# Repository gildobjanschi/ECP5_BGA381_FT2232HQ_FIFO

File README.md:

# ECP5/FT2232HQ Software & Hardware
This project implements a High Speed USB device using a FT2232HQ operating in synchronous FIFO mode coupled with a Lattice Semiconductor ECP5 FPGA. 

## Software
Read all the details of the bring-up steps and test code in the [Wiki](https://github.com/gildobjanschi/ECP5_BGA381_FT2232HQ_FIFO/wiki).

The diagram below will help you understand the software architecture and navigate the Verilog and C source code a bit easier.

## Hardware
The board is fully functional. An [extension board](https://github.com/gildobjanschi/ECP5_BGA381_FT2232HQ_FIFO_EXT) was developed to help validate the design.

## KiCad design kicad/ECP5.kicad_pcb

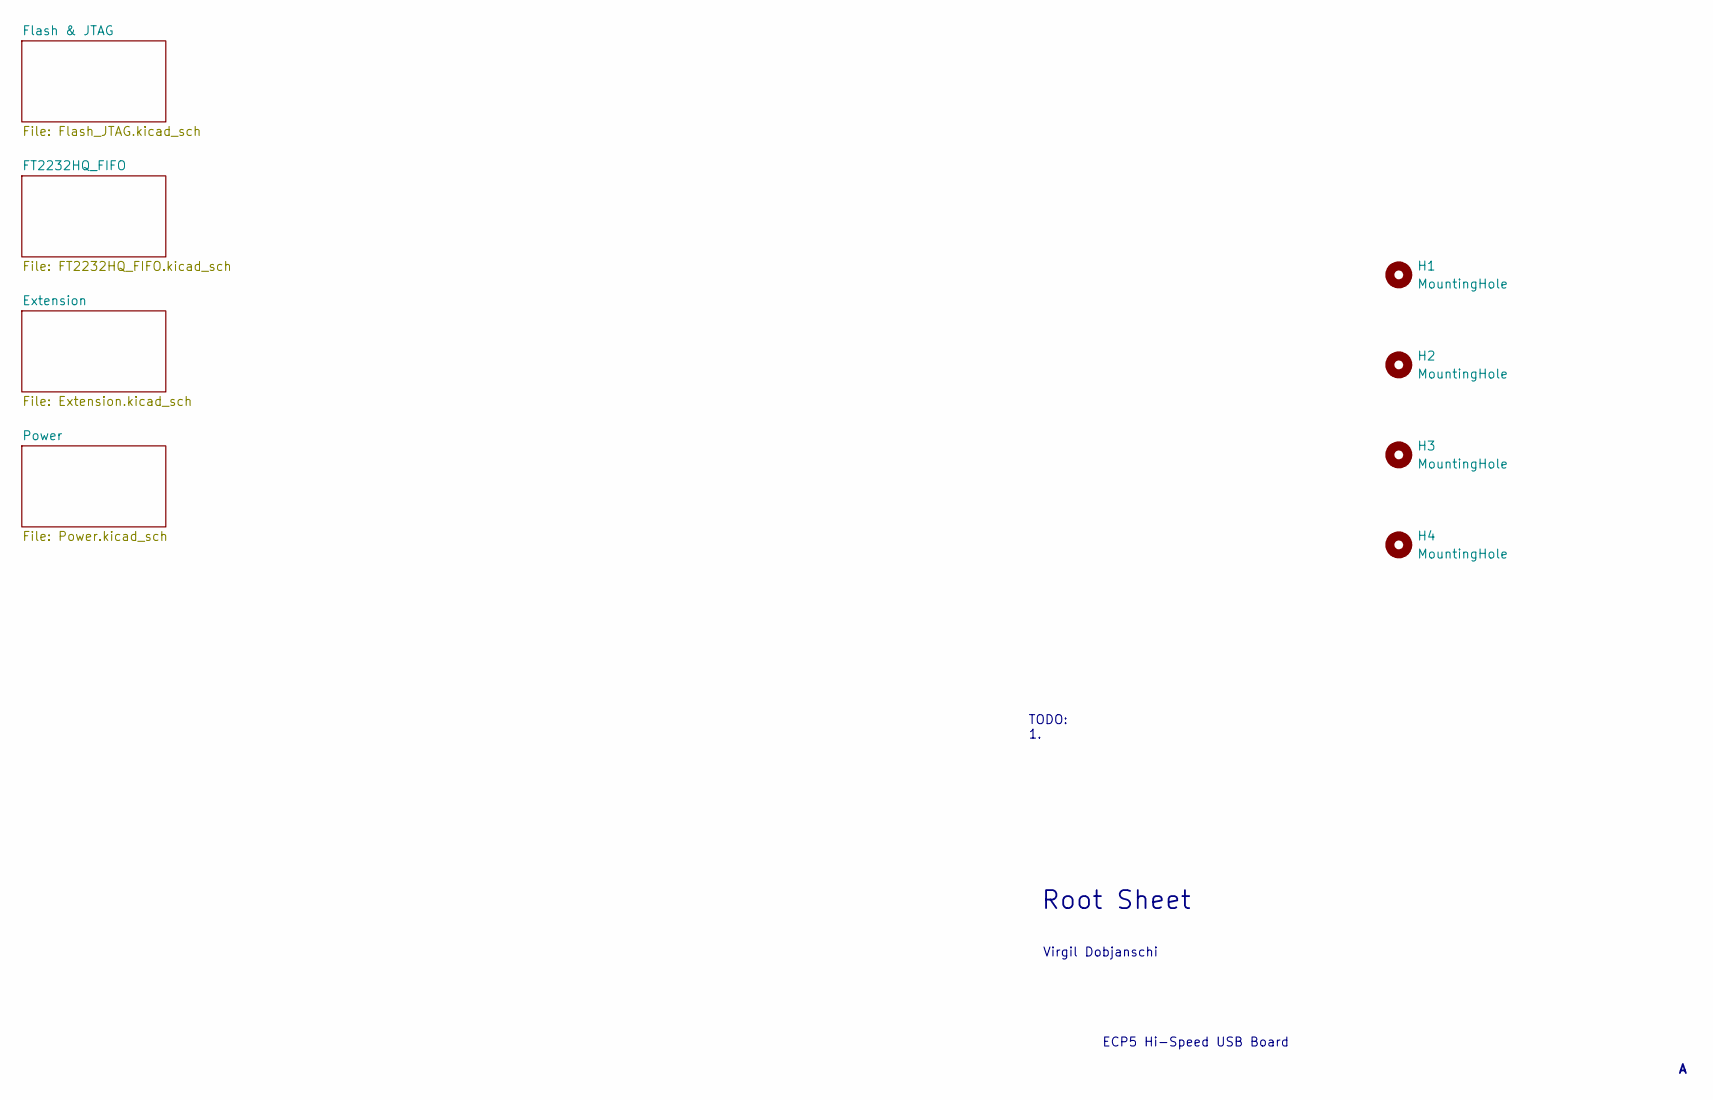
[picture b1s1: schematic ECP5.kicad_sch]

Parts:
H1, H2, H3, H4: MountingHole; MountingHole_3.2mm_M3

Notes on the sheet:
ECP5 Hi-Speed USB Board
Root Sheet
Virgil Dobjanschi
TODO: 1.

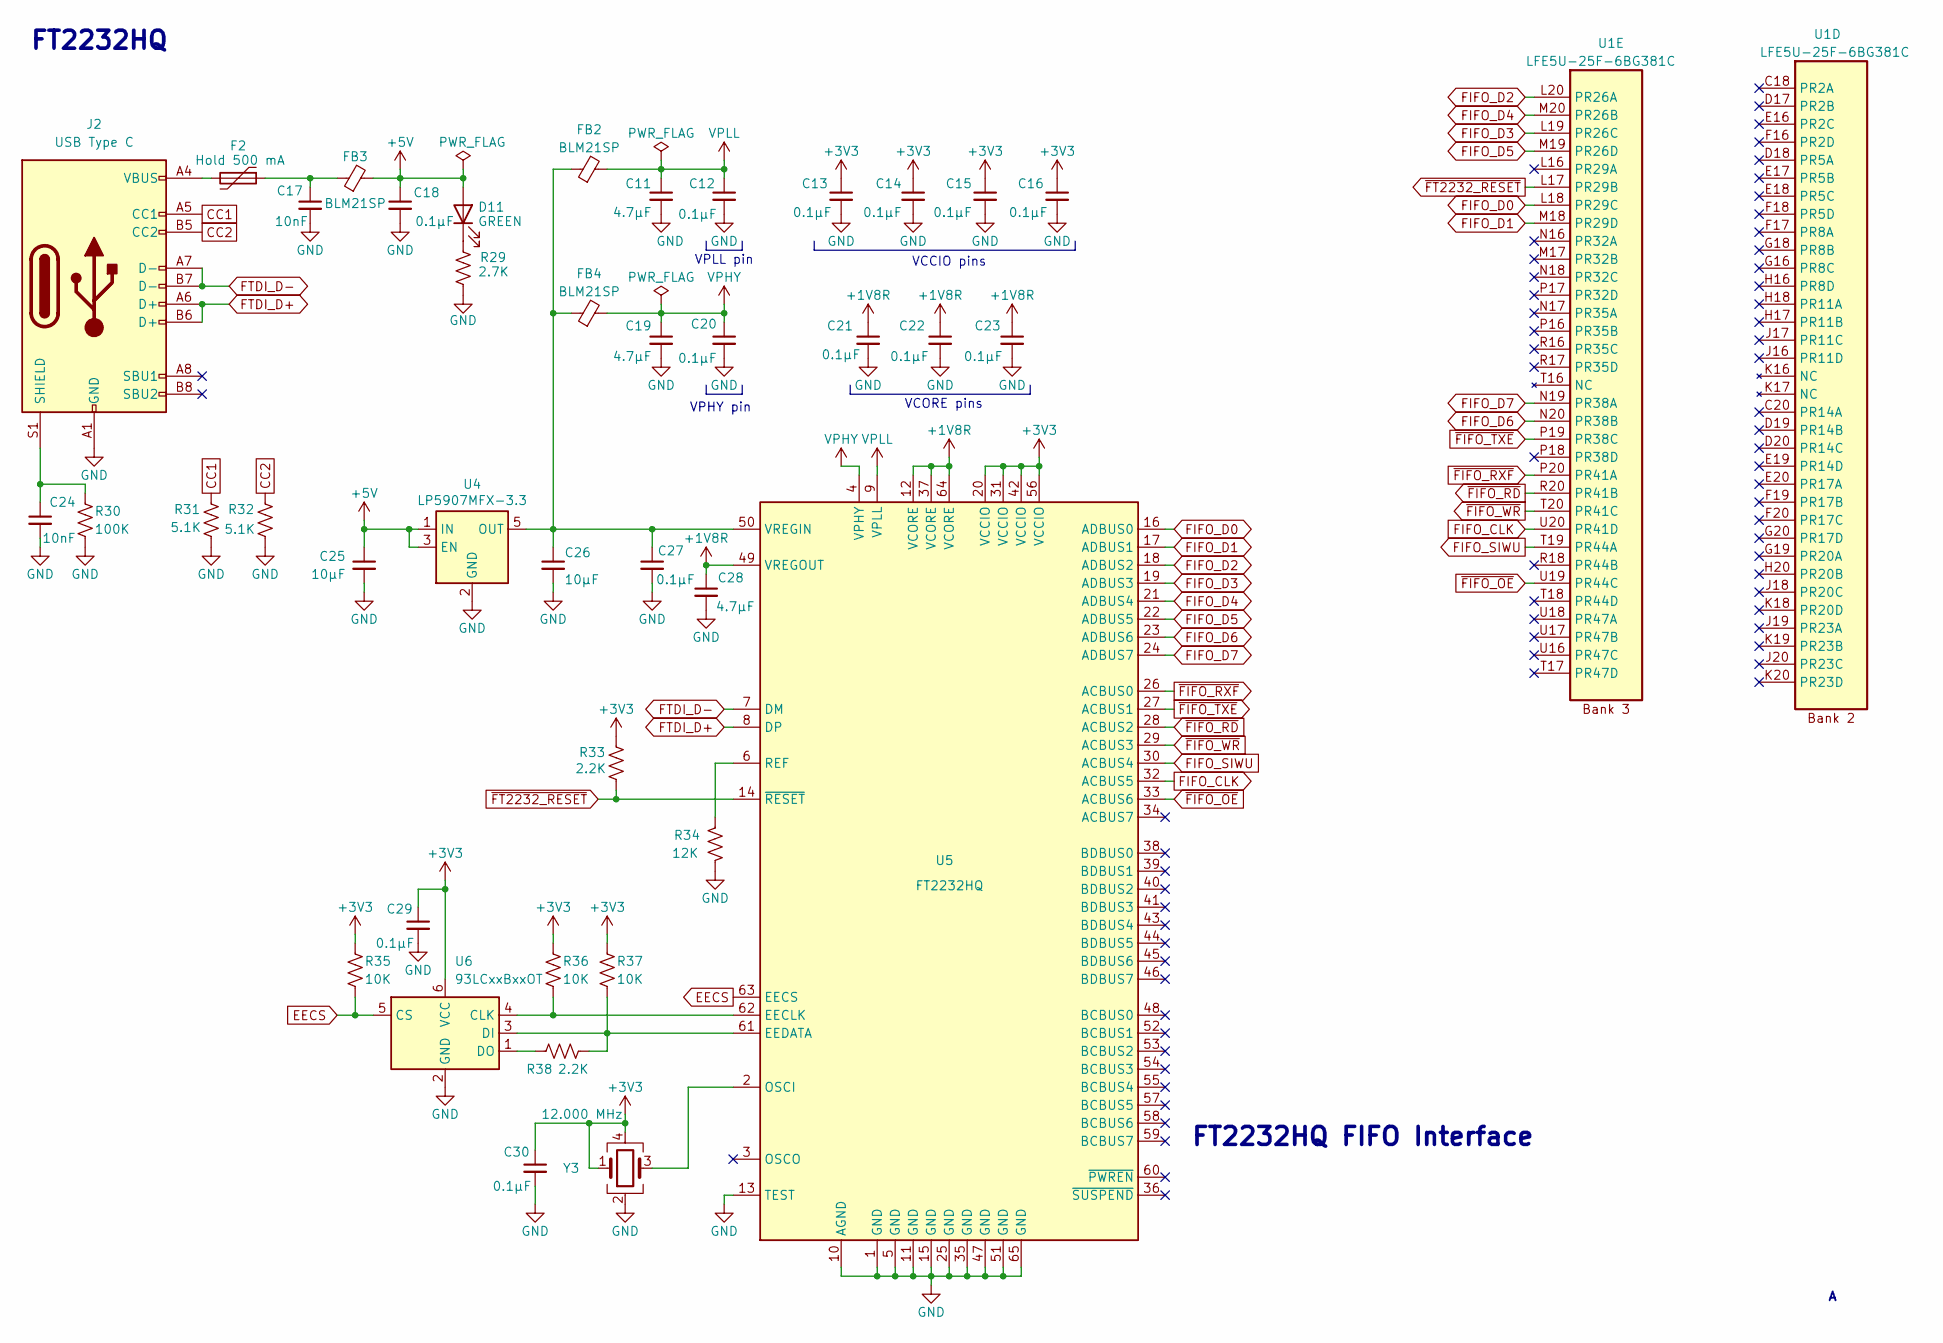
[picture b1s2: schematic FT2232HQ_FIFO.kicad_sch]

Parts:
C11, C19, C28: 4.7µF; C_0603_1608Metric; MPN CL10A475KP8NNNC
C12, C13, C14, C15, C16, C18, C20, C21, C22, C23, C27, C29, C30: 0.1µF; C_0603_1608Metric; MPN CL10B104KB8NNNC
C17, C24: 10nF; C_0603_1608Metric; MPN CL10B103KB8NNWC
C25, C26: 10µF; C_0805_2012Metric; MPN CL21B106KOQNNNE
D11: GREEN; LED_0603_1608Metric; MPN APT1608LZGCK
F2: Hold 500 mA; Fuse_1812_4532Metric; MPN 0ZCG0050AF2C
FB2, FB3, FB4: BLM21SP; L_0805_2012Metric; MPN BLM21SP601SN1D
J2: USB Type C; USB_C_Receptacle_GCT_USB4105-xx-A_16P_TopMnt_Horizontal; MPN USB4105-GF-A-120
R29: 2.7K; R_0603_1608Metric; MPN ERJ-3EKF2701V
R30: 100K; R_0603_1608Metric; MPN ERJ-3EKF1003V
R31, R32: 5.1K; R_0603_1608Metric; MPN ERJ-3EKF5101V
R33, R38: 2.2K; R_0603_1608Metric; MPN ERJ-3EKF2201V
R34: 12K; R_0603_1608Metric; MPN ERJ-3EKF1202V
R35, R36, R37: 10K; R_0603_1608Metric; MPN ERJ-3EKF1002V
U1: LFE5U-25F-6BG381C; BGA-381_pitch0.8mm_dia0.4mm; MPN LFE5U-25F-6BG381C
U4: LP5907MFX-3.3; SOT-23-5; MPN LP5907MFX-3.3/NOPB
U5: FT2232HQ; QFN-64-1EP_9x9mm_P0.5mm_EP4.35x4.35mm; MPN FT2232HQ-REEL
U6: 93LCxxBxxOT; SOT-23-6; MPN 93LC56BT-I/OT
Y3: 12.000 MHz; Oscillator_SMD_ECS_2520MV-xxx-xx-4Pin_2.5x2.0mm; MPN SG-210STF 12.0000ML3

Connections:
+1V8R: C21.1, C22.1, C23.1, C28.1, U5.12 (VCORE), U5.37 (VCORE), U5.49 (VREGOUT), U5.64 (VCORE)
+3V3: C13.1, C14.1, C15.1, C16.1, C29.1, C30.1, R33.1, R35.1, R36.1, R37.1, U5.20 (VCCIO), U5.31 (VCCIO), U5.42 (VCCIO), U5.56 (VCCIO), U6.6 (VCC), Y3.1, Y3.4; also elsewhere on the board
+5V: C18.1, C25.1, D11.2 (A), FB3.2, U4.1 (IN), U4.3 (EN); also elsewhere on the board
CC1: J2.A5 (CC1), R31.1
CC2: J2.B5 (CC2), R32.1
EECS: R35.2, U5.63 (EECS), U6.5 (CS)
FIFO_CLK: U1.U20 (PR41D), U5.32 (ACBUS5)
FIFO_D0: U1.L18 (PR29C), U5.16 (ADBUS0)
FIFO_D1: U1.M18 (PR29D), U5.17 (ADBUS1)
FIFO_D2: U1.L20 (PR26A), U5.18 (ADBUS2)
FIFO_D3: U1.L19 (PR26C), U5.19 (ADBUS3)
FIFO_D4: U1.M20 (PR26B), U5.21 (ADBUS4)
FIFO_D5: U1.M19 (PR26D), U5.22 (ADBUS5)
FIFO_D6: U1.N20 (PR38B), U5.23 (ADBUS6)
FIFO_D7: U1.N19 (PR38A), U5.24 (ADBUS7)
FIFO_SIWU: U1.T19 (PR44A), U5.30 (ACBUS4)
FTDI_D+: J2.A6 (D+), J2.B6 (D+), U5.8 (DP)
FTDI_D-: J2.A7 (D-), J2.B7 (D-), U5.7 (DM)
GND: C11.2, C12.2, C13.2, C14.2, C15.2, C16.2, C17.2, C18.2, C19.2, C20.2, C21.2, C22.2, C23.2, C24.2, C25.2, C26.2, C27.2, C28.2, C29.2, C30.2, J2.A1 (GND), J2.A12 (GND), J2.B1 (GND), J2.B12 (GND), R29.2, R30.2, R31.2, R32.2, R34.2, U4.2 (GND), U5.1 (GND), U5.5 (GND), U5.10 (AGND), U5.11 (GND), U5.13 (TEST), U5.15 (GND), U5.25 (GND), U5.35 (GND), U5.47 (GND), U5.51 (GND), U5.65 (GND), U6.2 (GND), Y3.2; also elsewhere on the board
unnamed: C17.1, F2.1, FB3.1
unnamed: D11.1 (K), R29.1
unnamed: F2.2, J2.A4 (VBUS), J2.A9 (VBUS), J2.B4 (VBUS), J2.B9 (VBUS)
unnamed: C24.1, J2.S1 (SHIELD), R30.1
unnamed: C26.1, C27.1, FB2.1, FB4.1, U4.5 (OUT), U5.50 (VREGIN)
unnamed: R36.2, U5.62 (EECLK), U6.4 (CLK)
unnamed: R37.2, R38.2, U5.61 (EEDATA), U6.3 (DI)
unnamed: U5.2 (OSCI), Y3.3
unnamed: R34.1, U5.6 (REF)
unnamed: R38.1, U6.1 (DO)
VPHY: C19.1, C20.1, FB4.2, U5.4 (VPHY)
VPLL: C11.1, C12.1, FB2.2, U5.9 (VPLL)
~FIFO_OE: U1.U19 (PR44C), U5.33 (ACBUS6)
~FIFO_RD: U1.R20 (PR41B), U5.28 (ACBUS2)
~FIFO_RXF: U1.P20 (PR41A), U5.26 (ACBUS0)
~FIFO_TXE: U1.P19 (PR38C), U5.27 (ACBUS1)
~FIFO_WR: U1.T20 (PR41C), U5.29 (ACBUS3)
~FT2232_RESET: R33.2, U1.L17 (PR29B), U5.14 (~RESET)

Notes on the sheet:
VPHY pin
VPLL pin
FT2232HQ
VCCIO pins
VCORE pins
FT2232HQ FIFO Interface

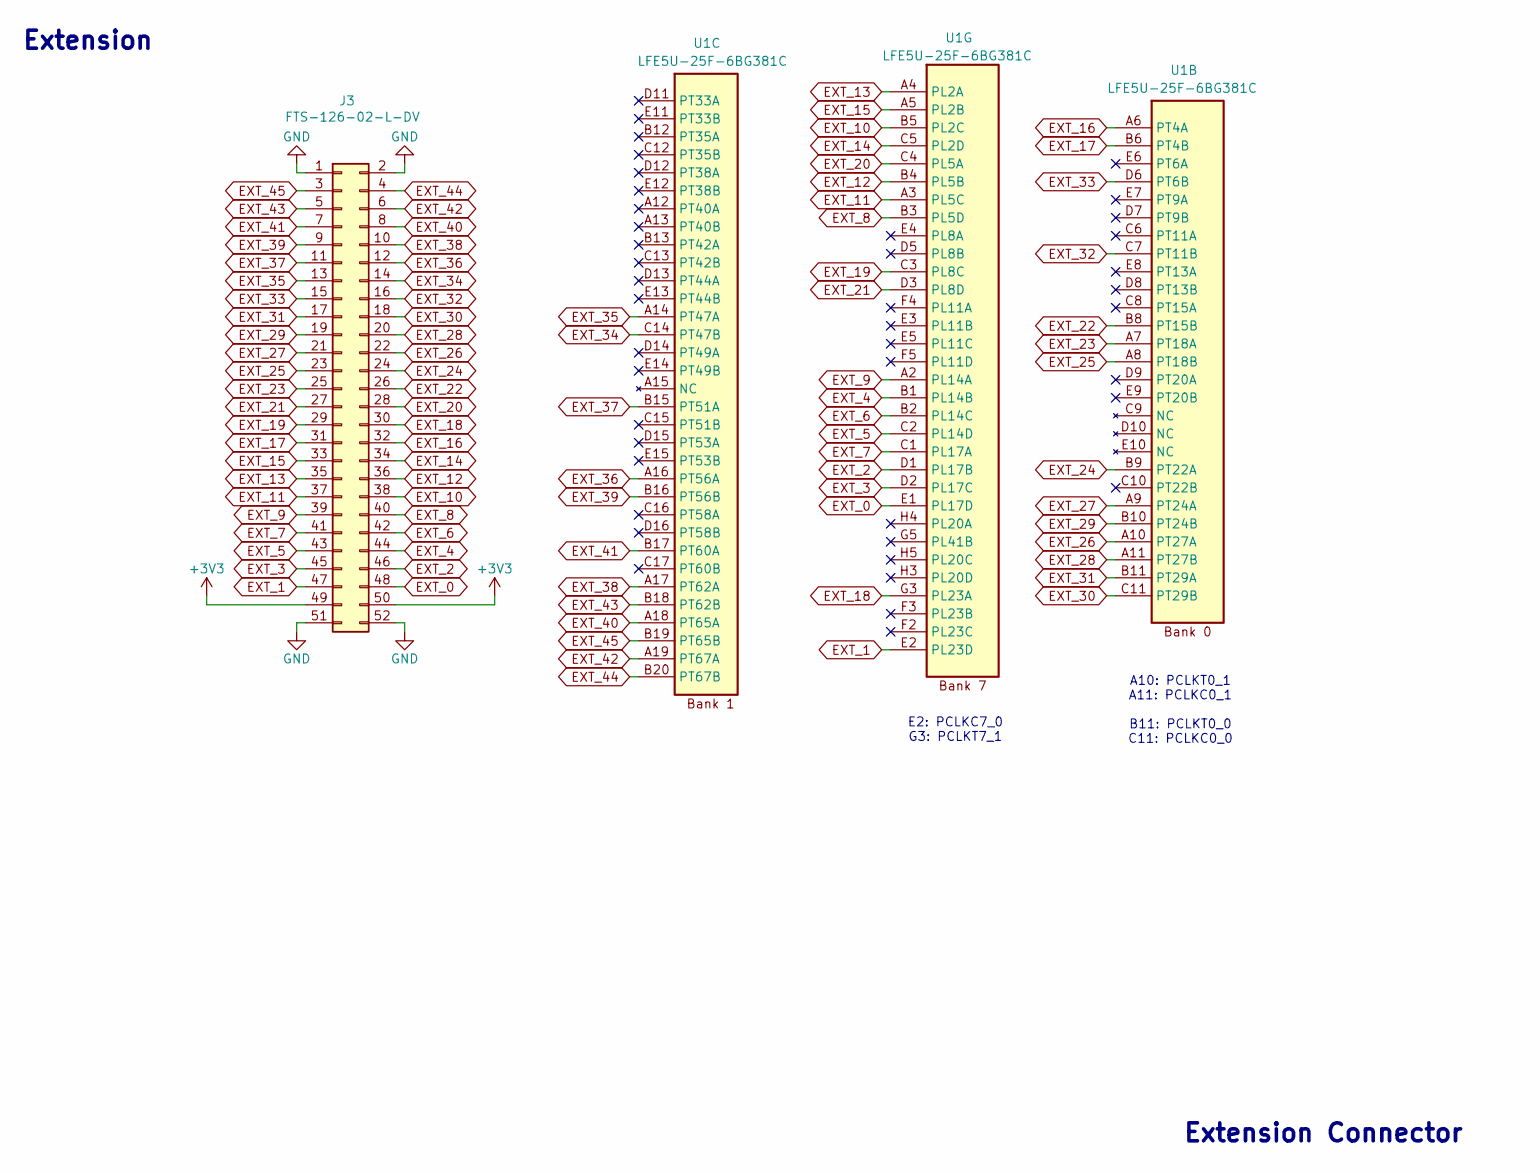
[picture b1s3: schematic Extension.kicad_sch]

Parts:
J3: FTS-126-02-L-DV; SAMTEC-FTS-126-02-X-DV; MPN FTS-126-02-L-DV
U1: LFE5U-25F-6BG381C; BGA-381_pitch0.8mm_dia0.4mm; MPN LFE5U-25F-6BG381C

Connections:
+3V3: J3.49, J3.50; also elsewhere on the board
EXT_0: J3.48, U1.E1 (PL17D)
EXT_1: J3.47, U1.E2 (PL23D)
EXT_2: J3.46, U1.D1 (PL17B)
EXT_3: J3.45, U1.D2 (PL17C)
EXT_4: J3.44, U1.B1 (PL14B)
EXT_5: J3.43, U1.C2 (PL14D)
EXT_6: J3.42, U1.B2 (PL14C)
EXT_7: J3.41, U1.C1 (PL17A)
EXT_8: J3.40, U1.B3 (PL5D)
EXT_9: J3.39, U1.A2 (PL14A)
EXT_10: J3.38, U1.B5 (PL2C)
EXT_11: J3.37, U1.A3 (PL5C)
EXT_12: J3.36, U1.B4 (PL5B)
EXT_13: J3.35, U1.A4 (PL2A)
EXT_14: J3.34, U1.C5 (PL2D)
EXT_15: J3.33, U1.A5 (PL2B)
EXT_16: J3.32, U1.A6 (PT4A)
EXT_17: J3.31, U1.B6 (PT4B)
EXT_18: J3.30, U1.G3 (PL23A)
EXT_19: J3.29, U1.C3 (PL8C)
EXT_20: J3.28, U1.C4 (PL5A)
EXT_21: J3.27, U1.D3 (PL8D)
EXT_22: J3.26, U1.B8 (PT15B)
EXT_23: J3.25, U1.A7 (PT18A)
EXT_24: J3.24, U1.B9 (PT22A)
EXT_25: J3.23, U1.A8 (PT18B)
EXT_26: J3.22, U1.A10 (PT27A)
EXT_27: J3.21, U1.A9 (PT24A)
EXT_28: J3.20, U1.A11 (PT27B)
EXT_29: J3.19, U1.B10 (PT24B)
EXT_30: J3.18, U1.C11 (PT29B)
EXT_31: J3.17, U1.B11 (PT29A)
EXT_32: J3.16, U1.C7 (PT11B)
EXT_33: J3.15, U1.D6 (PT6B)
EXT_34: J3.14, U1.C14 (PT47B)
EXT_35: J3.13, U1.A14 (PT47A)
EXT_36: J3.12, U1.A16 (PT56A)
EXT_37: J3.11, U1.B15 (PT51A)
EXT_38: J3.10, U1.A17 (PT62A)
EXT_39: J3.9, U1.B16 (PT56B)
EXT_40: J3.8, U1.A18 (PT65A)
EXT_41: J3.7, U1.B17 (PT60A)
EXT_42: J3.6, U1.A19 (PT67A)
EXT_43: J3.5, U1.B18 (PT62B)
EXT_44: J3.4, U1.B20 (PT67B)
EXT_45: J3.3, U1.B19 (PT65B)
GND: J3.1, J3.2, J3.51, J3.52; also elsewhere on the board

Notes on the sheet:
E2: PCLKC7_0 G3: PCLKT7_1
Extension Connector
Extension
A10: PCLKT0_1 A11: PCLKC0_1 B11: PCLKT0_0 C11: PCLKC0_0

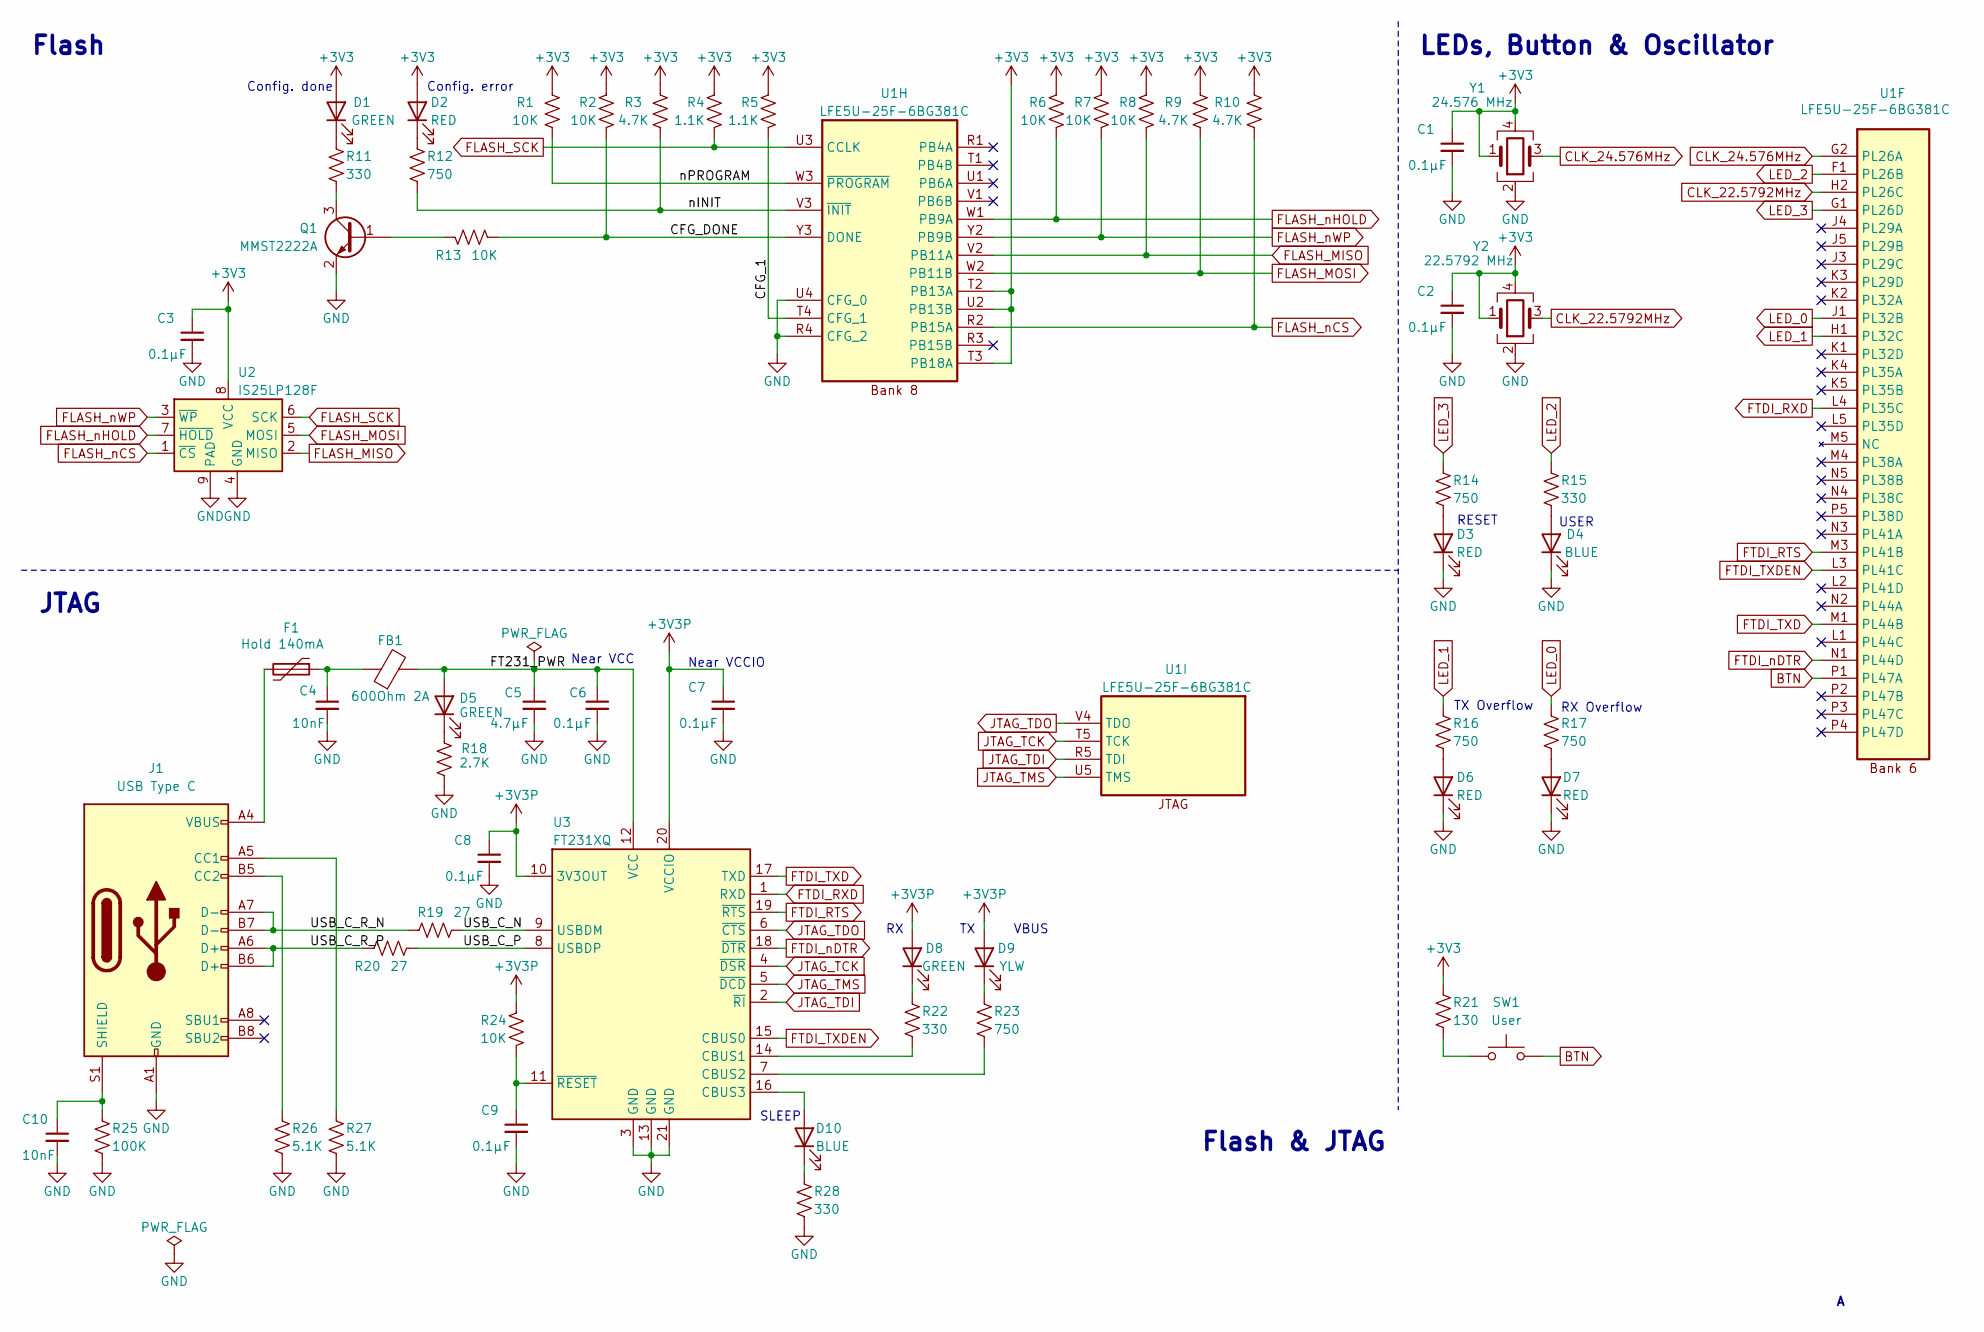
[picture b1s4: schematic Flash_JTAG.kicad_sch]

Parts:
C1, C2, C3, C6, C7, C8, C9: 0.1µF; C_0603_1608Metric; MPN CL10B104KB8NNNC
C4, C10: 10nF; C_0603_1608Metric; MPN CL10B103KB8NNWC
C5: 4.7µF; C_0603_1608Metric; MPN CL10A475KP8NNNC
D1, D5, D8: GREEN; LED_0603_1608Metric; MPN APT1608LZGCK
D2, D3, D6, D7: RED; LED_0603_1608Metric; MPN APT1608LSECK/J3-PRV
D4, D10: BLUE; LED_0603_1608Metric; MPN APT1608LVBC/D
D9: YLW; LED_0603_1608Metric; MPN APT1608LSYCK/J3-PRV
F1: Hold 140mA; Fuse_1812_4532Metric; MPN 0ZCG0014FF2C
FB1: 600Ohm 2A; L_0805_2012Metric; MPN 78279220601
J1: USB Type C; USB_C_Receptacle_GCT_USB4105-xx-A_16P_TopMnt_Horizontal; MPN USB4105-GF-A-120
Q1: MMST2222A; SOT-323_SC-70; MPN MMST2222A-7-F
R1, R2, R6, R7, R8, R13, R24: 10K; R_0603_1608Metric; MPN ERJ-3EKF1002V
R3, R9, R10: 4.7K; R_0603_1608Metric; MPN ERJ-3EKF4701V
R4, R5: 1.1K; R_0603_1608Metric; MPN ERJ-3EKF1101V
R11, R15, R22, R28: 330; R_0603_1608Metric; MPN ERJ-3EKF3300V
R12, R14, R16, R17, R23: 750; R_0603_1608Metric; MPN ERJ-3EKF7500V
R18: 2.7K; R_0603_1608Metric; MPN ERJ-3EKF2701V
R19, R20: 27; R_0603_1608Metric; MPN ERJ-3EKF27R0V
R21: 130; R_0603_1608Metric; MPN ERJ-3EKF1300V
R25: 100K; R_0603_1608Metric; MPN ERJ-3EKF1003V
R26, R27: 5.1K; R_0603_1608Metric; MPN ERJ-3EKF5101V
SW1: User; SW_SPST_PTS645; MPN PTS645SK43SMTR92 LFS
U1: LFE5U-25F-6BG381C; BGA-381_pitch0.8mm_dia0.4mm; MPN LFE5U-25F-6BG381C
U2: IS25LP128F; WSON-8-1EP_6x5mm_P1.27mm_EP3.4x4.3mm; MPN IS25LP128-JKLE
U3: FT231XQ; QFN-20-1EP_4x4mm_P0.5mm_EP2.5x2.5mm; MPN FT231XQ-R
Y1: 24.576 MHz; Oscillator_SMD_Abracon_ASE-4Pin_3.2x2.5mm; MPN 830207659209
Y2: 22.5792 MHz; Oscillator_SMD_Abracon_ASE-4Pin_3.2x2.5mm; MPN 830207659009

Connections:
+3V3: C1.1, C2.1, C3.1, D1.2 (A), D2.2 (A), R1.2, R2.1, R3.2, R4.1, R5.1, R6.1, R7.1, R8.1, R9.2, R10.2, R21.1, U1.T2 (PB13A), U1.T3 (PB18A), U1.U2 (PB13B), U2.8 (VCC), Y1.1, Y1.4, Y2.1, Y2.4; also elsewhere on the board
+3V3P: C7.1, C8.1, D8.2 (A), D9.2 (A), R24.1, U3.10 (3V3OUT), U3.20 (VCCIO)
/Flash & JTAG/CFG_1: R5.2, U1.T4 (CFG_1)
/Flash & JTAG/CFG_DONE: R2.2, R13.2, U1.Y3 (DONE)
/Flash & JTAG/FT231_PWR: C5.1, C6.1, D5.2 (A), FB1.2, U3.12 (VCC)
/Flash & JTAG/USB_C_N: R19.2, U3.9 (USBDM)
/Flash & JTAG/USB_C_P: R20.2, U3.8 (USBDP)
/Flash & JTAG/USB_C_R_N: J1.A7 (D-), J1.B7 (D-), R19.1
/Flash & JTAG/USB_C_R_P: J1.A6 (D+), J1.B6 (D+), R20.1
/Flash & JTAG/nINIT: R3.1, R12.2, U1.V3 (~INIT)
/Flash & JTAG/nPROGRAM: R1.1, U1.W3 (~PROGRAM)
BTN: SW1.2, U1.P1 (PL47A)
CLK_22.5792MHz: U1.H2 (PL26C), Y2.3
CLK_24.576MHz: U1.G2 (PL26A), Y1.3
FLASH_MISO: R8.2, U1.V2 (PB11A), U2.2 (MISO)
FLASH_MOSI: R9.1, U1.W2 (PB11B), U2.5 (MOSI)
FLASH_SCK: R4.2, U1.U3 (CCLK), U2.6 (SCK)
FLASH_nCS: R10.1, U1.R2 (PB15A), U2.1 (~CS)
FLASH_nHOLD: R6.2, U1.W1 (PB9A), U2.7 (~HOLD)
FLASH_nWP: R7.2, U1.Y2 (PB9B), U2.3 (~WP)
FTDI_RTS: U1.M3 (PL41B), U3.19 (~RTS)
FTDI_RXD: U1.L4 (PL35C), U3.1 (RXD)
FTDI_TXD: U1.M1 (PL44B), U3.17 (TXD)
FTDI_TXDEN: U1.L3 (PL41C), U3.15 (CBUS0)
FTDI_nDTR: U1.N1 (PL44D), U3.18 (~DTR)
GND: C1.2, C2.2, C3.2, C4.2, C5.2, C6.2, C7.2, C8.2, C9.2, C10.2, D3.1 (K), D4.1 (K), D6.1 (K), D7.1 (K), J1.A1 (GND), J1.A12 (GND), J1.B1 (GND), J1.B12 (GND), Q1.2 (E), R18.2, R25.2, R26.2, R27.2, R28.2, U1.R4 (CFG_2), U1.U4 (CFG_0), U2.4 (GND), U2.9 (PAD), U3.3 (GND), U3.13 (GND), U3.21 (GND), Y1.2, Y2.2; also elsewhere on the board
JTAG_TCK: U1.T5 (TCK), U3.4 (~DSR)
JTAG_TDI: U1.R5 (TDI), U3.2 (~RI)
JTAG_TDO: U1.V4 (TDO), U3.6 (~CTS)
JTAG_TMS: U1.U5 (TMS), U3.5 (~DCD)
LED_0: R17.1, U1.J1 (PL32B)
LED_1: R16.1, U1.H1 (PL32C)
LED_2: R15.1, U1.F1 (PL26B)
LED_3: R14.1, U1.G1 (PL26D)
unnamed: C4.1, F1.1, FB1.1
unnamed: D1.1 (K), R11.1
unnamed: D2.1 (K), R12.1
unnamed: D3.2 (A), R14.2
unnamed: D4.2 (A), R15.2
unnamed: D5.1 (K), R18.1
unnamed: D6.2 (A), R16.2
unnamed: D7.2 (A), R17.2
unnamed: D8.1 (K), R22.1
unnamed: D9.1 (K), R23.1
unnamed: D10.2 (A), U3.16 (CBUS3)
unnamed: D10.1 (K), R28.1
unnamed: F1.2, J1.A4 (VBUS), J1.A9 (VBUS), J1.B4 (VBUS), J1.B9 (VBUS)
unnamed: J1.A5 (CC1), R27.1
unnamed: J1.B5 (CC2), R26.1
unnamed: C10.1, J1.S1 (SHIELD), R25.1
unnamed: Q1.1 (B), R13.1
unnamed: Q1.3 (C), R11.2
unnamed: R21.2, SW1.1
unnamed: R22.2, U3.14 (CBUS1)
unnamed: R23.2, U3.7 (CBUS2)
unnamed: C9.1, R24.2, U3.11 (~RESET)

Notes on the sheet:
Near VCCIO
Flash
Near VCC
Flash & JTAG
SLEEP
RX Overflow
LEDs, Button & Oscillator
RESET
VBUS
Config. done
JTAG
Config. error
USER
TX Overflow

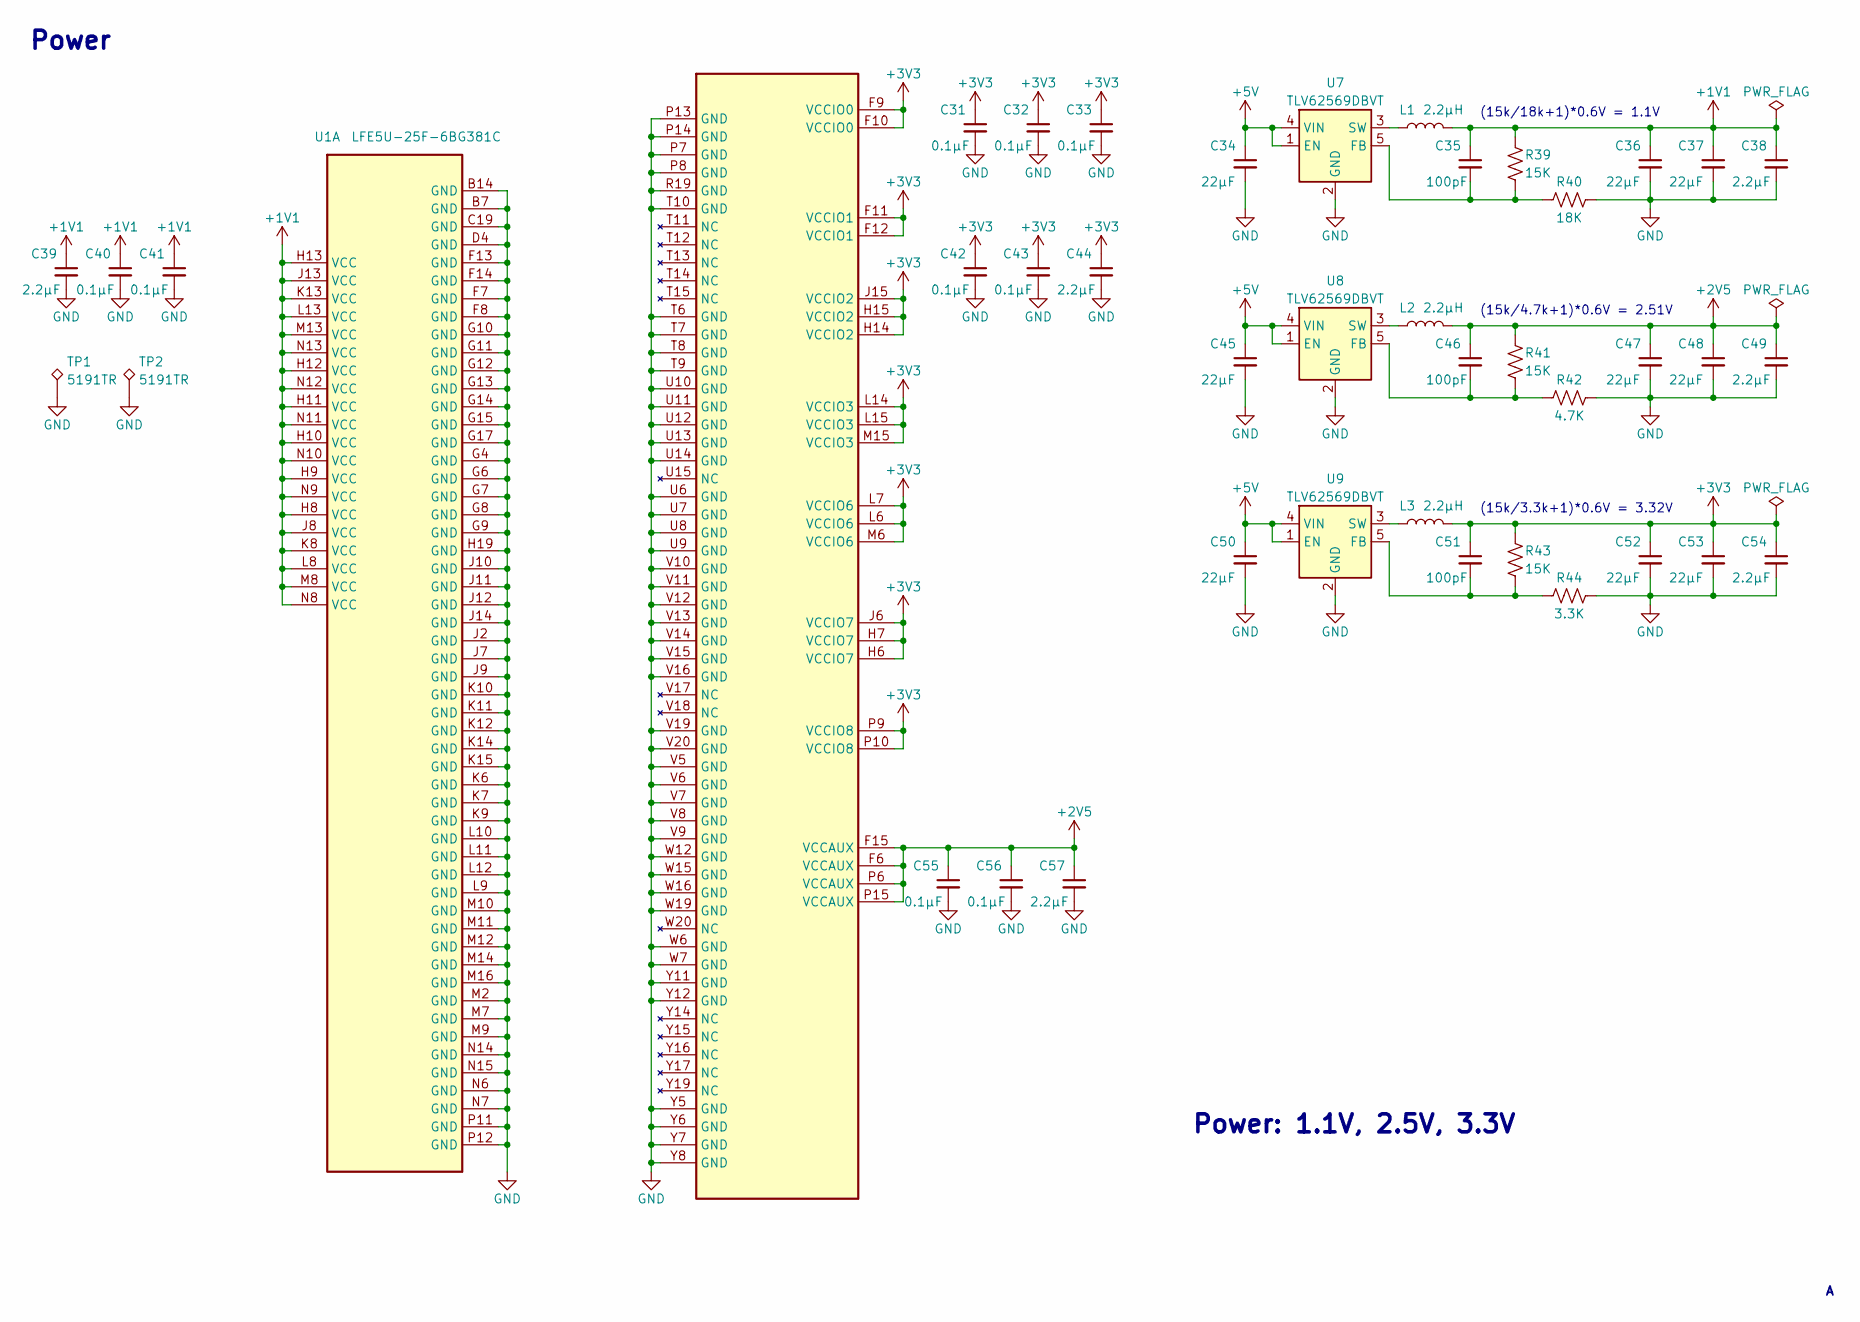
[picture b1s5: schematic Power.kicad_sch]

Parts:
C31, C32, C33, C40, C41, C42, C43, C55, C56: 0.1µF; C_0603_1608Metric; MPN CL10B104KB8NNNC
C34, C36, C37, C45, C47, C48, C50, C52, C53: 22µF; C_0603_1608Metric; MPN CL10A226MP8NUNE
C35, C46, C51: 100pF; C_0603_1608Metric; MPN CL10C101FB81PNC
C38, C39, C44, C49, C54, C57: 2.2µF; C_0603_1608Metric; MPN CL10B225KP8NNNC
L1, L2, L3: 2.2µH; L_1210_3225Metric; MPN DFE322512F-2R2M=P2
R39, R41, R43: 15K; R_0603_1608Metric; MPN ERJ-3EKF1502V
R40: 18K; R_0603_1608Metric; MPN ERJ-3EKF1802V
R42: 4.7K; R_0603_1608Metric; MPN ERJ-3EKF4701V
R44: 3.3K; R_0603_1608Metric; MPN ERJ-3EKF3301V
TP1, TP2: 5191TR; KEYSTONE_5197TR; MPN 5191TR
U1: LFE5U-25F-6BG381C; BGA-381_pitch0.8mm_dia0.4mm; MPN LFE5U-25F-6BG381C
U7, U8, U9: TLV62569DBVT; SOT-23-5; MPN TLV62569DBVT

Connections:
+1V1: C35.1, C36.1, C37.1, C38.1, C39.1, C40.1, C41.1, L1.2, R39.1, U1.H8 (VCC), U1.H9 (VCC), U1.H10 (VCC), U1.H11 (VCC), U1.H12 (VCC), U1.H13 (VCC), U1.J8 (VCC), U1.J13 (VCC), U1.K8 (VCC), U1.K13 (VCC), U1.L8 (VCC), U1.L13 (VCC), U1.M8 (VCC), U1.M13 (VCC), U1.N8 (VCC), U1.N9 (VCC), U1.N10 (VCC), U1.N11 (VCC), U1.N12 (VCC), U1.N13 (VCC)
+2V5: C46.1, C47.1, C48.1, C49.1, C55.1, C56.1, C57.1, L2.2, R41.1, U1.F6 (VCCAUX), U1.F15 (VCCAUX), U1.P6 (VCCAUX), U1.P15 (VCCAUX)
+3V3: C31.1, C32.1, C33.1, C42.1, C43.1, C44.1, C51.1, C52.1, C53.1, C54.1, L3.2, R43.1, U1.F9 (VCCIO0), U1.F10 (VCCIO0), U1.F11 (VCCIO1), U1.F12 (VCCIO1), U1.H6 (VCCIO7), U1.H7 (VCCIO7), U1.H14 (VCCIO2), U1.H15 (VCCIO2), U1.J6 (VCCIO7), U1.J15 (VCCIO2), U1.L6 (VCCIO6), U1.L7 (VCCIO6), U1.L14 (VCCIO3), U1.L15 (VCCIO3), U1.M6 (VCCIO6), U1.M15 (VCCIO3), U1.P9 (VCCIO8), U1.P10 (VCCIO8); also elsewhere on the board
+5V: C34.1, C45.1, C50.1, U7.1 (EN), U7.4 (VIN), U8.1 (EN), U8.4 (VIN), U9.1 (EN), U9.4 (VIN); also elsewhere on the board
GND: C31.2, C32.2, C33.2, C34.2, C36.2, C37.2, C38.2, C39.2, C40.2, C41.2, C42.2, C43.2, C44.2, C45.2, C47.2, C48.2, C49.2, C50.2, C52.2, C53.2, C54.2, C55.2, C56.2, C57.2, R40.2, R42.2, R44.2, TP1.1, TP2.1, U1.B7 (GND), U1.B14 (GND), U1.C19 (GND), U1.D4 (GND), U1.F7 (GND), U1.F8 (GND), U1.F13 (GND), U1.F14 (GND), U1.G4 (GND), U1.G6 (GND), U1.G7 (GND), U1.G8 (GND), U1.G9 (GND), U1.G10 (GND), U1.G11 (GND), U1.G12 (GND), U1.G13 (GND), U1.G14 (GND), U1.G15 (GND), U1.G17 (GND), U1.H19 (GND), U1.J2 (GND), U1.J7 (GND), U1.J9 (GND), U1.J10 (GND), U1.J11 (GND), U1.J12 (GND), U1.J14 (GND), U1.K6 (GND), U1.K7 (GND), U1.K9 (GND), U1.K10 (GND), U1.K11 (GND), U1.K12 (GND), U1.K14 (GND), U1.K15 (GND), U1.L9 (GND), U1.L10 (GND), U1.L11 (GND), U1.L12 (GND), U1.M2 (GND), U1.M7 (GND), U1.M9 (GND), U1.M10 (GND), U1.M11 (GND), U1.M12 (GND), U1.M14 (GND), U1.M16 (GND), U1.N6 (GND), U1.N7 (GND), U1.N14 (GND), U1.N15 (GND), U1.P7 (GND), U1.P8 (GND), U1.P11 (GND), U1.P12 (GND), U1.P13 (GND), U1.P14 (GND), U1.R19 (GND), U1.T6 (GND), U1.T7 (GND), U1.T8 (GND), U1.T9 (GND), U1.T10 (GND), U1.U6 (GND), U1.U7 (GND), U1.U8 (GND), U1.U9 (GND), U1.U10 (GND), U1.U11 (GND), U1.U12 (GND), U1.U13 (GND), U1.U14 (GND), U1.V5 (GND), U1.V6 (GND), U1.V7 (GND), U1.V8 (GND), U1.V9 (GND), U1.V10 (GND), U1.V11 (GND), U1.V12 (GND), U1.V13 (GND), U1.V14 (GND), U1.V15 (GND), U1.V16 (GND), U1.V19 (GND), U1.V20 (GND), U1.W6 (GND), U1.W7 (GND), U1.W12 (GND), U1.W15 (GND), U1.W16 (GND), U1.W19 (GND), U1.Y5 (GND), U1.Y6 (GND), U1.Y7 (GND), U1.Y8 (GND), U1.Y11 (GND), U1.Y12 (GND), U7.2 (GND), U8.2 (GND), U9.2 (GND); also elsewhere on the board
unnamed: C35.2, R39.2, R40.1, U7.5 (FB)
unnamed: L1.1, U7.3 (SW)
unnamed: C46.2, R41.2, R42.1, U8.5 (FB)
unnamed: L2.1, U8.3 (SW)
unnamed: C51.2, R43.2, R44.1, U9.5 (FB)
unnamed: L3.1, U9.3 (SW)

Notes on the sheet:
Power
(15k/3.3k+1)*0.6V = 3.32V
(15k/18k+1)*0.6V = 1.1V
(15k/4.7k+1)*0.6V = 2.51V
Power: 1.1V, 2.5V, 3.3V

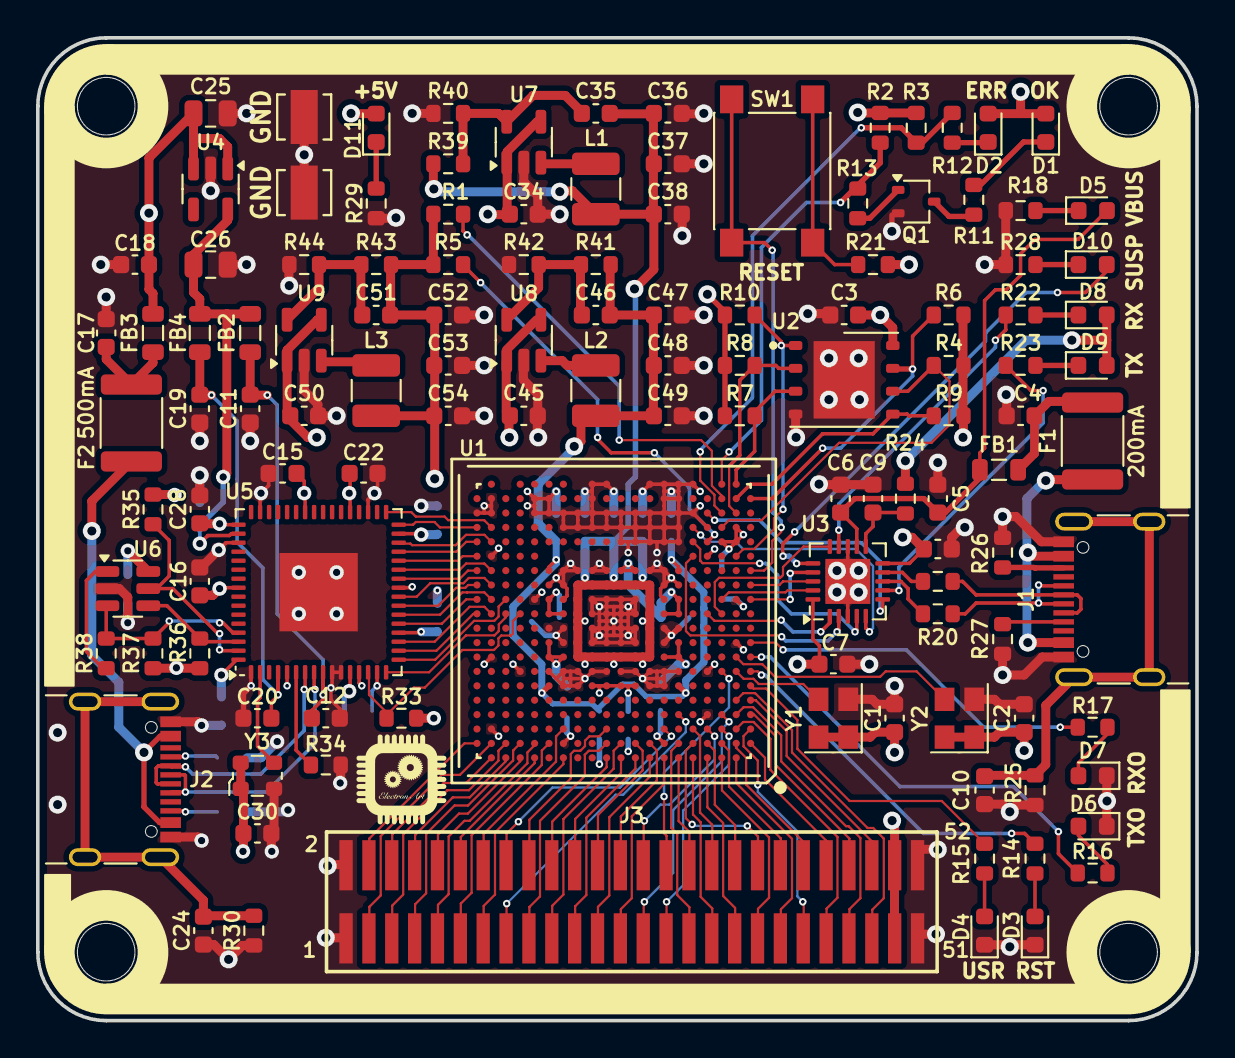
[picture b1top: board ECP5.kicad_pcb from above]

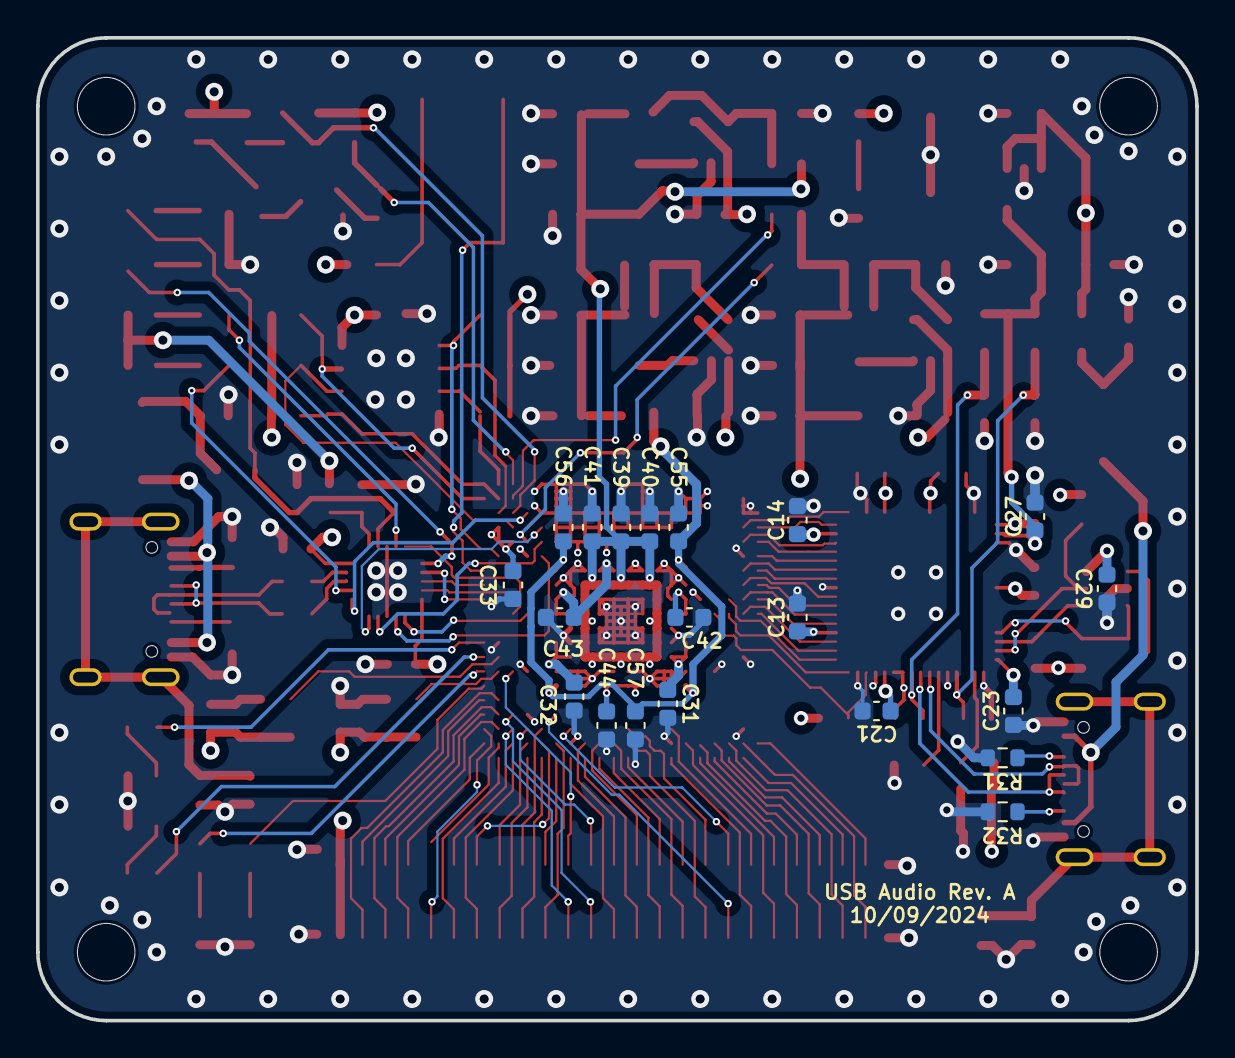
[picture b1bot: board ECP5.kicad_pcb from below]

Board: 4 copper layers, 64.4 x 54.6 mm, 144 parts (20 on the bottom side), 145 nets.

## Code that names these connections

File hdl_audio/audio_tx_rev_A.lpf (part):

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#LOCATE COMP "jtag_tck" SITE "T5"; # FTDI_nDSR FPGA receives
#LOCATE COMP "jtag_tms" SITE "U5"; # FTDI_nDCD FPGA receives

#IOBUF PORT "jtag_tdi" PULLMODE=UP IO_TYPE=LVCMOS33 DRIVE=4;
#IOBUF PORT "jtag_tdo" PULLMODE=UP IO_TYPE=LVCMOS33 DRIVE=4;
#IOBUF PORT "jtag_tck" PULLMODE=UP IO_TYPE=LVCMOS33 DRIVE=4;
#IOBUF PORT "jtag_tms" PULLMODE=UP IO_TYPE=LVCMOS33 DRIVE=4;

######### SPI Flash chip #########
LOCATE COMP "flash_csn" SITE "R2";
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
IOBUF PORT "flash_csn" PULLMODE=UP IO_TYPE=LVCMOS33 DRIVE=4;
IOBUF PORT "flash_clk" PULLMODE=DOWN IO_TYPE=LVCMOS33 DRIVE=4;
IOBUF PORT "flash_mosi" PULLMODE=UP IO_TYPE=LVCMOS33 DRIVE=4;
IOBUF PORT "flash_miso" PULLMODE=UP IO_TYPE=LVCMOS33 DRIVE=4;
IOBUF PORT "flash_holdn" PULLMODE=UP IO_TYPE=LVCMOS33 DRIVE=4;
IOBUF PORT "flash_wpn" PULLMODE=UP IO_TYPE=LVCMOS33 DRIVE=4;

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LOCATE COMP "ftdi_dtrn" SITE "N1"; # FPGA receives
LOCATE COMP "ftdi_txden" SITE "L3"; # FPGA receives

IOBUF PORT "ftdi_rxd" PULLMODE=UP IO_TYPE=LVCMOS33 DRIVE=4;
IOBUF PORT "ftdi_txd" PULLMODE=UP IO_TYPE=LVCMOS33;
IOBUF PORT "ftdi_rtsn" PULLMODE=UP IO_TYPE=LVCMOS33;
IOBUF PORT "ftdi_dtrn" PULLMODE=UP IO_TYPE=LVCMOS33;
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
IOBUF PORT "ft2232_reset_n" PULLMODE=UP IO_TYPE=LVCMOS33 OPENDRAIN=ON;
IOBUF PORT "fifo_oe_n" PULLMODE=NONE IO_TYPE=LVCMOS33 DRIVE=4;
IOBUF PORT "fifo_clk" PULLMODE=NONE IO_TYPE=LVCMOS33 DRIVE=4;
IOBUF PORT "fifo_siwu" PULLMODE=UP IO_TYPE=LVCMOS33 DRIVE=4;
IOBUF PORT "fifo_wr_n" PULLMODE=NONE IO_TYPE=LVCMOS33 DRIVE=4;
IOBUF PORT "fifo_rd_n" PULLMODE=NONE IO_TYPE=LVCMOS33 DRIVE=4;
IOBUF PORT "fifo_txe_n" PULLMODE=NONE IO_TYPE=LVCMOS33 DRIVE=4;
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LOCATE COMP "led_reset" SITE "G1";
LOCATE COMP "led_user" SITE "F1";

IOBUF PORT "led_0" PULLMODE=NONE IO_TYPE=LVCMOS33 DRIVE=4;
IOBUF PORT "led_1" PULLMODE=NONE IO_TYPE=LVCMOS33 DRIVE=4;
IOBUF PORT "led_reset" PULLMODE=NONE IO_TYPE=LVCMOS33 DRIVE=4;
IOBUF PORT "led_user" PULLMODE=NONE IO_TYPE=LVCMOS33 DRIVE=4;

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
